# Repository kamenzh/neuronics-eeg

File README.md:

# Neuronic

An open development project for an affordable eight-channel EEG acquisition
PCB, ESP32 wireless streaming and PC-based signal processing and classification.

**Current revision: A0 — schematic and unrouted placement for bench review.**
There is no manufactured or body-validated Neuronic board yet. This repository
contains genuine KiCad source, not a manufacturing release.

**First time using KiCad? Read [START_HERE](docs/START_HERE.md).** Open
[`hardware/kicad/neuronic.kicad_pro`](hardware/kicad/neuronic.kicad_pro) in KiCad.

## System

```mermaid
flowchart TD
    E["8 contacts + reference"] --> P["Input networks"]
    P --> A["ADS1299: PGAs and simultaneous ADCs"]
    A -->|"3.3 V SPI"| M["External ESP32"]
    A --> B["Limited bias output: tenth contact"]
    M -->|"Wireless"| C["PC: recording and classification"]
    V["Battery and regulators"] --> A
```

| Parameter | A0 design target |
| --- | --- |
| Recording channels | 8 simultaneous |
| Contacts | 8 recording + 1 reference + 1 bias |
| Front end | ADS1299IPAG, programmable gain, 24-bit output |
| Initial rate | 250 samples/s/channel |
| Analog / ADC digital supplies | 5 V / 3.3 V |
| Input power | External 7-9 V battery pack; no charger |
| Controller interface | Generic 12-pin 3.3 V SPI header |
| PCB | 88 x 80 mm, four copper layers, placed and unrouted |

The ADS1299 already supplies the amplification and conversion. An additional
high-gain analog amplifier chain is not assumed. Nominal ADC bit depth is not
a claim of noise-free resolution, and more gain can reduce offset headroom.

## Repository map

| Path | Contents |
| --- | --- |
| `hardware/kicad/` | Main project, three schematic sheets, PCB, custom symbols and bundled footprints |
| `hardware/bom/` | Per-component review BOM; not an order list |
| `hardware/design.json` | Generated component/net/placement record |
| `hardware/validation/` | Exported netlist, connectivity audit, DRC, RC calculation and sheet previews |
| `hardware/fabrication/` | Release policy; no order-ready Gerbers |
| `firmware/` | Acquisition firmware specification; implementation pending |
| `software/` | PC receiver/recorder specification; implementation pending |
| `ml/` | Evaluation plan; no trained classifier yet |
| `experiments/` | Recording and validation protocols |
| `docs/` | Beginner guide, design decisions, open blockers and bench plan |
| `tools/` | Reproducible hardware generator and validation commands |
| `data/` | Local private recordings; contents ignored by Git |

The old CortexLink README is retained in `docs/archive/initial-README.md`.
The empty duplicate KiCad scaffolds were removed; their originals remain in
the repository history at `ae7d76e`.

## Verification

Read [the current status](hardware/validation/STATUS.md) before using the files.
Checks compare the **actual KiCad-exported netlist** with the source, component
footprints and an independent physical pin contract. They do not prove analog
performance, layout quality or body safety.

```bash
python tools/check_design.py
python tools/simulate_input.py
python tools/validate_kicad.py --kicad-cli /path/to/kicad-cli
```

The last command requires KiCad 8 or newer for CLI ERC/DRC. This unrouted
checkpoint is expected to fail release checks; errors are not excluded to
make the output look clean. GUI ERC/DRC instructions are in the beginner guide.

## Roadmap

- [x] Consolidate project and document circuit decisions.
- [x] Create editable KiCad sheets, footprint bundle, BOM and placed PCB.
- [x] Export and audit connectivity; perform limited ideal RC calculation.
- [ ] Close input-protection, connector, bias-loop and power-review blockers.
- [ ] Complete layout, plane design, routing, ERC and schematic-parity DRC.
- [ ] Select exact stocked parts and compare delivered assembly quotes.
- [ ] Fabricate a small prototype batch and complete bench tests.
- [ ] Implement and verify acquisition, raw recording and loss accounting.
- [ ] Review final body-connected design before scalp testing.
- [ ] Record repeatable EEG, then evaluate baselines and a CNN across sessions.

## Experiments and safety

The immediate target is trustworthy acquisition and a repeatable alpha
experiment. Intentional command classification follows measured signal quality.
EEG does not directly reveal arbitrary thoughts. Eye and muscle artifacts must
be checked, and train/test data must be separated by complete trials/sessions.

This is a body-connected engineering project, not a diagnostic device. A0 is
for bench development only. Do not attach it to a person. Final electrode
protection and fault paths need qualified review before any scalp recording.
Battery power, ERC and DRC alone do not establish safety. During approved
recording, use a self-contained battery arrangement and wireless communication,
with USB, chargers and mains-connected instruments disconnected.

## Sources and licensing

See [design decisions and primary sources](docs/DESIGN_DECISIONS.md),
[open blockers](docs/REVIEW_BLOCKERS.md) and [third-party notices](hardware/licenses/).
The repository's existing MIT license is preserved for original work. Bundled
KiCad library assets retain their own license and design-use exception. No
third-party EEG hardware project has been silently relicensed or included.

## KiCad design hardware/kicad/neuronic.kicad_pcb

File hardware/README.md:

# Hardware

Open `kicad/neuronic.kicad_pro`. Read `validation/STATUS.md` and
`../docs/START_HERE.md` first.

`design.json` is generated by `tools/generate_hardware.py` and describes the
component/net/placement checkpoint. It is not a substitute for the actual
KiCad schematic or DRC. `bom/bom-review.csv` lists candidate parts and unresolved
MPNs; it is not a purchase-ready BOM.

KiCad source, script and review docs belong in Git. Fabrication files should
only be exported for reviewed, tagged hardware revisions.

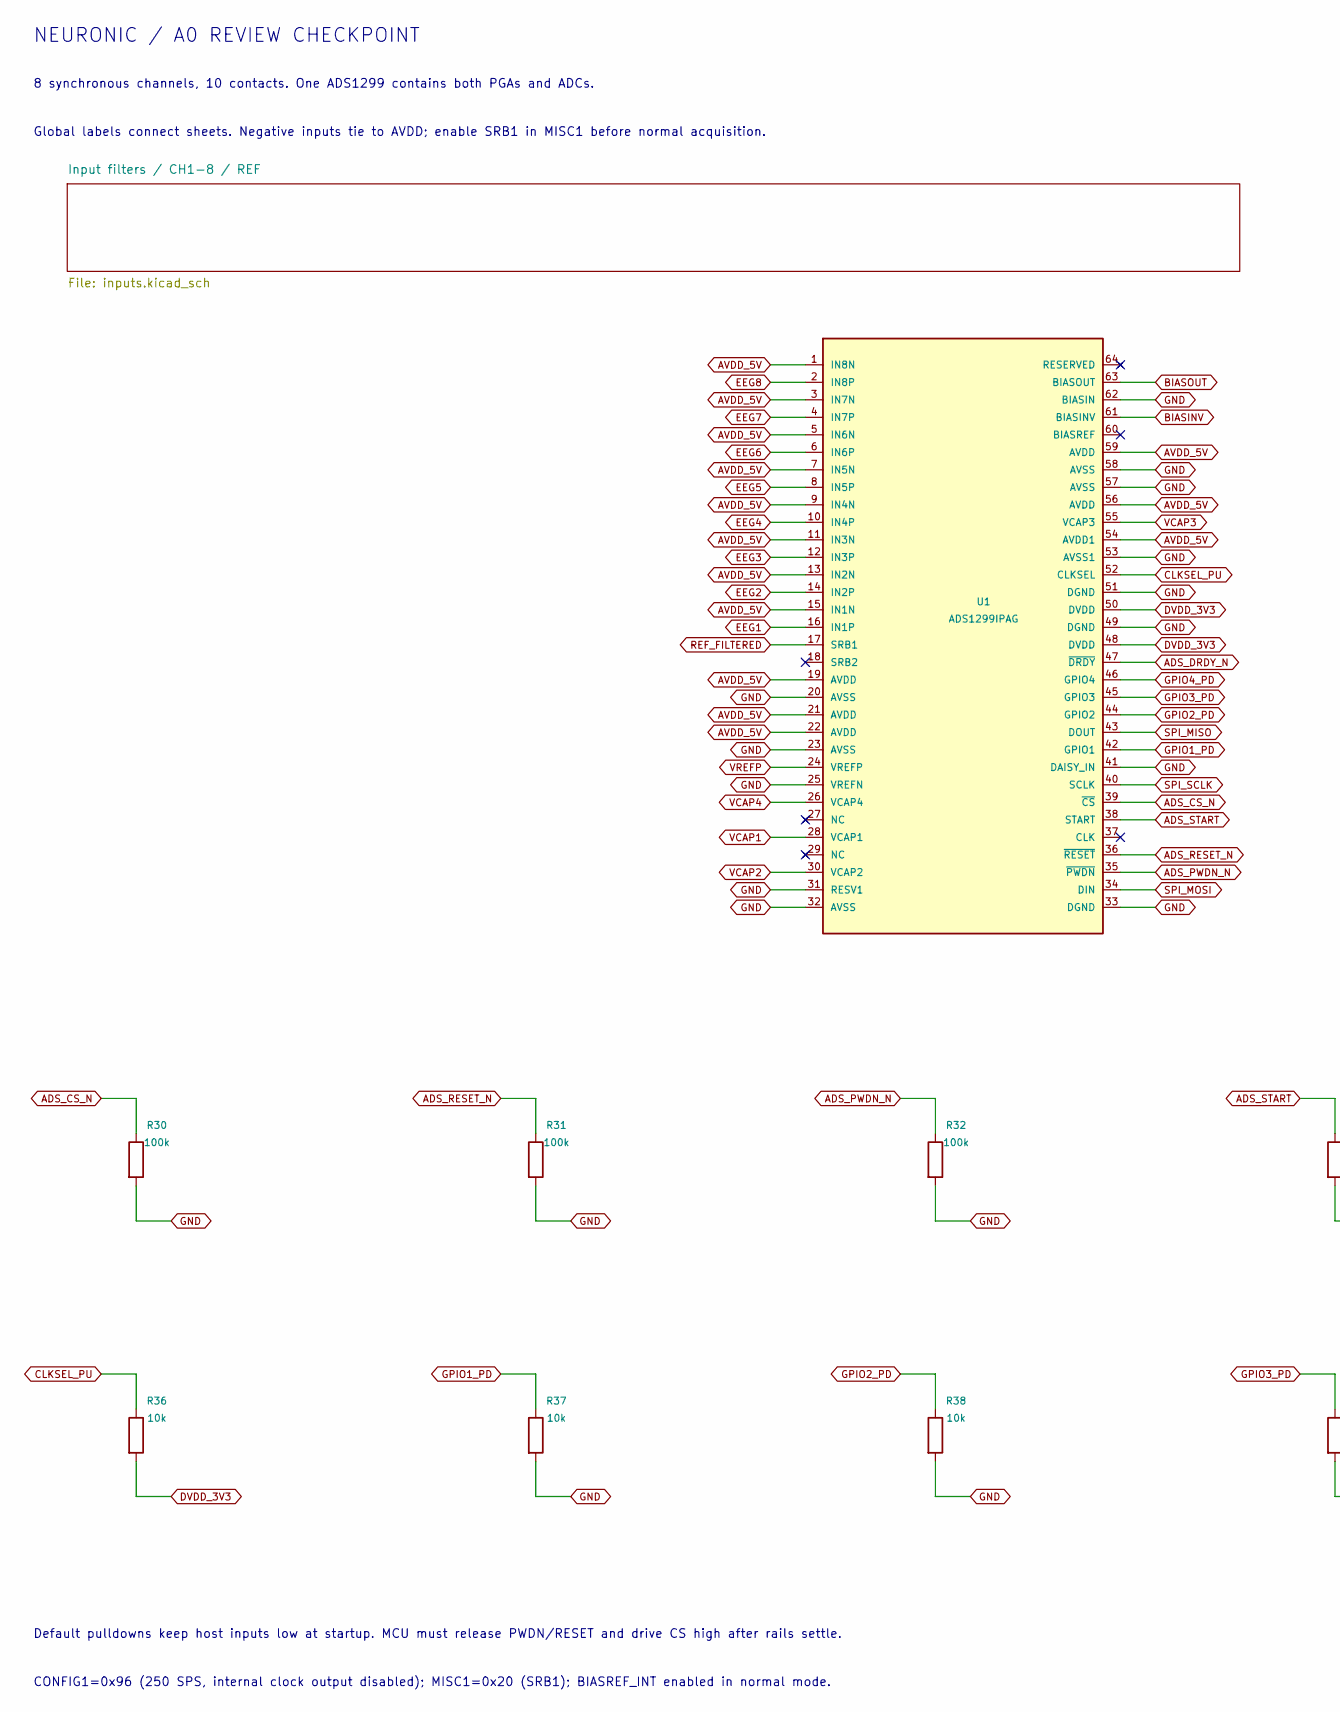
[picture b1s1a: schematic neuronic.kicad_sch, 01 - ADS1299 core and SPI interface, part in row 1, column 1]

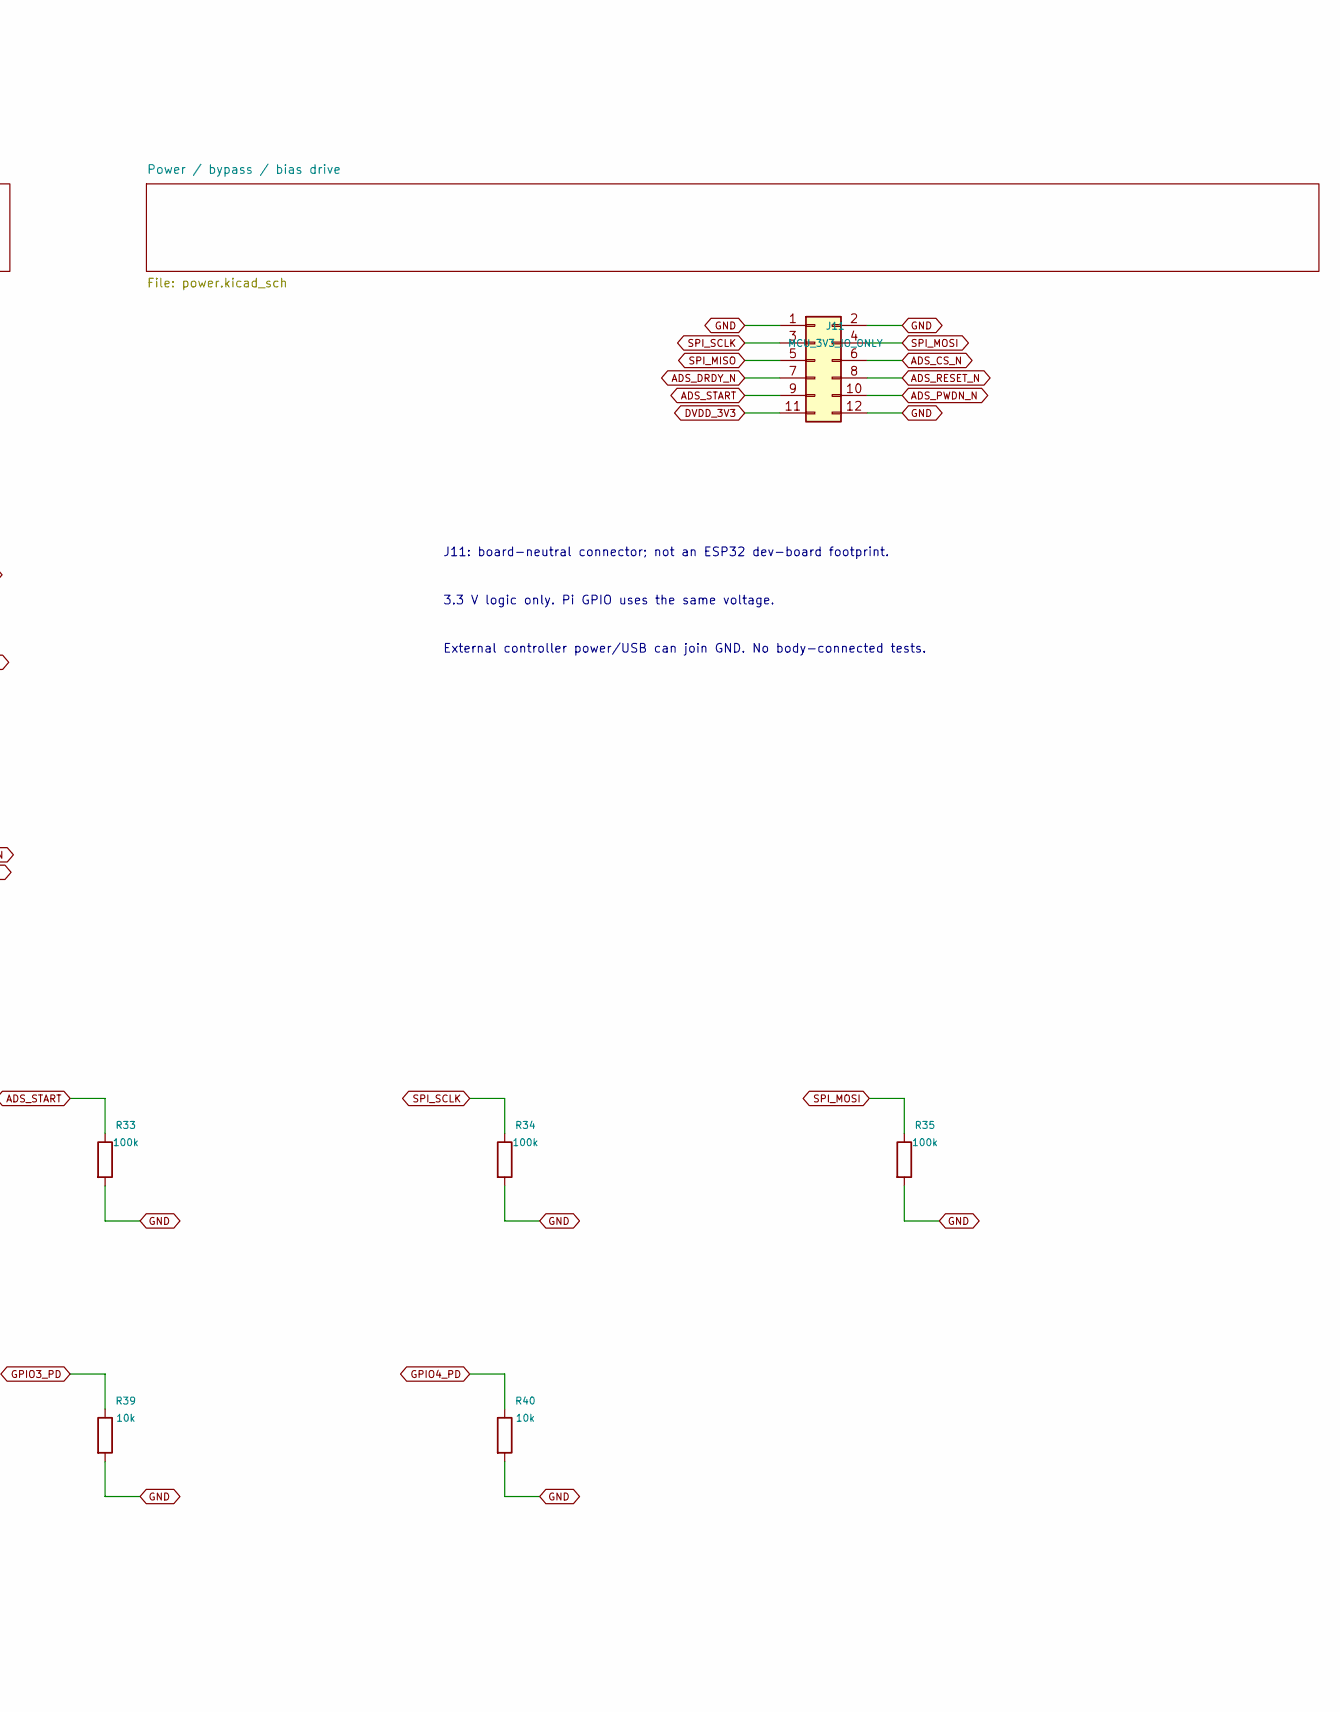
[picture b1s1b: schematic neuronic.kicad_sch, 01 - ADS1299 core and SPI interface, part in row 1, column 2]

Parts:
J11: MCU_3V3_IO_ONLY; PinHeader_2x06_P2.54mm_Vertical
R30, R31, R32, R33, R34, R35: 100k; R_0805_2012Metric
R36, R37, R38, R39, R40: 10k; R_0805_2012Metric
U1: ADS1299IPAG; TQFP-64_10x10mm_P0.5mm

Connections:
ADS_CS_N: J11.6, R30.1, U1.39 (~CS)
ADS_DRDY_N: J11.7, U1.47 (~DRDY)
ADS_PWDN_N: J11.10, R32.1, U1.35 (~PWDN)
ADS_RESET_N: J11.8, R31.1, U1.36 (~RESET)
ADS_START: J11.9, R33.1, U1.38 (START)
AVDD_5V: U1.1 (IN8N), U1.3 (IN7N), U1.5 (IN6N), U1.7 (IN5N), U1.9 (IN4N), U1.11 (IN3N), U1.13 (IN2N), U1.15 (IN1N), U1.19 (AVDD), U1.21 (AVDD), U1.22 (AVDD), U1.54 (AVDD1), U1.56 (AVDD), U1.59 (AVDD); also elsewhere on the board
BIASINV: U1.61 (BIASINV); also elsewhere on the board
BIASOUT: U1.63 (BIASOUT); also elsewhere on the board
CLKSEL_PU: R36.1, U1.52 (CLKSEL)
DVDD_3V3: J11.11, R36.2, U1.48 (DVDD), U1.50 (DVDD); also elsewhere on the board
EEG1: U1.16 (IN1P); also elsewhere on the board
EEG2: U1.14 (IN2P); also elsewhere on the board
EEG3: U1.12 (IN3P); also elsewhere on the board
EEG4: U1.10 (IN4P); also elsewhere on the board
EEG5: U1.8 (IN5P); also elsewhere on the board
EEG6: U1.6 (IN6P); also elsewhere on the board
EEG7: U1.4 (IN7P); also elsewhere on the board
EEG8: U1.2 (IN8P); also elsewhere on the board
GND: J11.1, J11.2, J11.12, R30.2, R31.2, R32.2, R33.2, R34.2, R35.2, R37.2, R38.2, R39.2, R40.2, U1.20 (AVSS), U1.23 (AVSS), U1.25 (VREFN), U1.31 (RESV1), U1.32 (AVSS), U1.33 (DGND), U1.41 (DAISY_IN), U1.49 (DGND), U1.51 (DGND), U1.53 (AVSS1), U1.57 (AVSS), U1.58 (AVSS), U1.62 (BIASIN); also elsewhere on the board
GPIO1_PD: R37.1, U1.42 (GPIO1)
GPIO2_PD: R38.1, U1.44 (GPIO2)
GPIO3_PD: R39.1, U1.45 (GPIO3)
GPIO4_PD: R40.1, U1.46 (GPIO4)
REF_FILTERED: U1.17 (SRB1); also elsewhere on the board
SPI_MISO: J11.5, U1.43 (DOUT)
SPI_MOSI: J11.4, R35.1, U1.34 (DIN)
SPI_SCLK: J11.3, R34.1, U1.40 (SCLK)
VCAP1: U1.28 (VCAP1); also elsewhere on the board
VCAP2: U1.30 (VCAP2); also elsewhere on the board
VCAP3: U1.55 (VCAP3); also elsewhere on the board
VCAP4: U1.26 (VCAP4); also elsewhere on the board
VREFP: U1.24 (VREFP); also elsewhere on the board

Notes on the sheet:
NEURONIC / A0 REVIEW CHECKPOINT
8 synchronous channels, 10 contacts. One ADS1299 contains both PGAs and ADCs.
Global labels connect sheets. Negative inputs tie to AVDD; enable SRB1 in MISC1 before normal acquisition.
J11: board-neutral connector; not an ESP32 dev-board footprint.
3.3 V logic only. Pi GPIO uses the same voltage.
External controller power/USB can join GND. No body-connected tests.
Default pulldowns keep host inputs low at startup. MCU must release PWDN/RESET and drive CS high after rails settle.
CONFIG1=0x96 (250 SPS, internal clock output disabled); MISC1=0x20 (SRB1); BIASREF_INT enabled in normal mode.

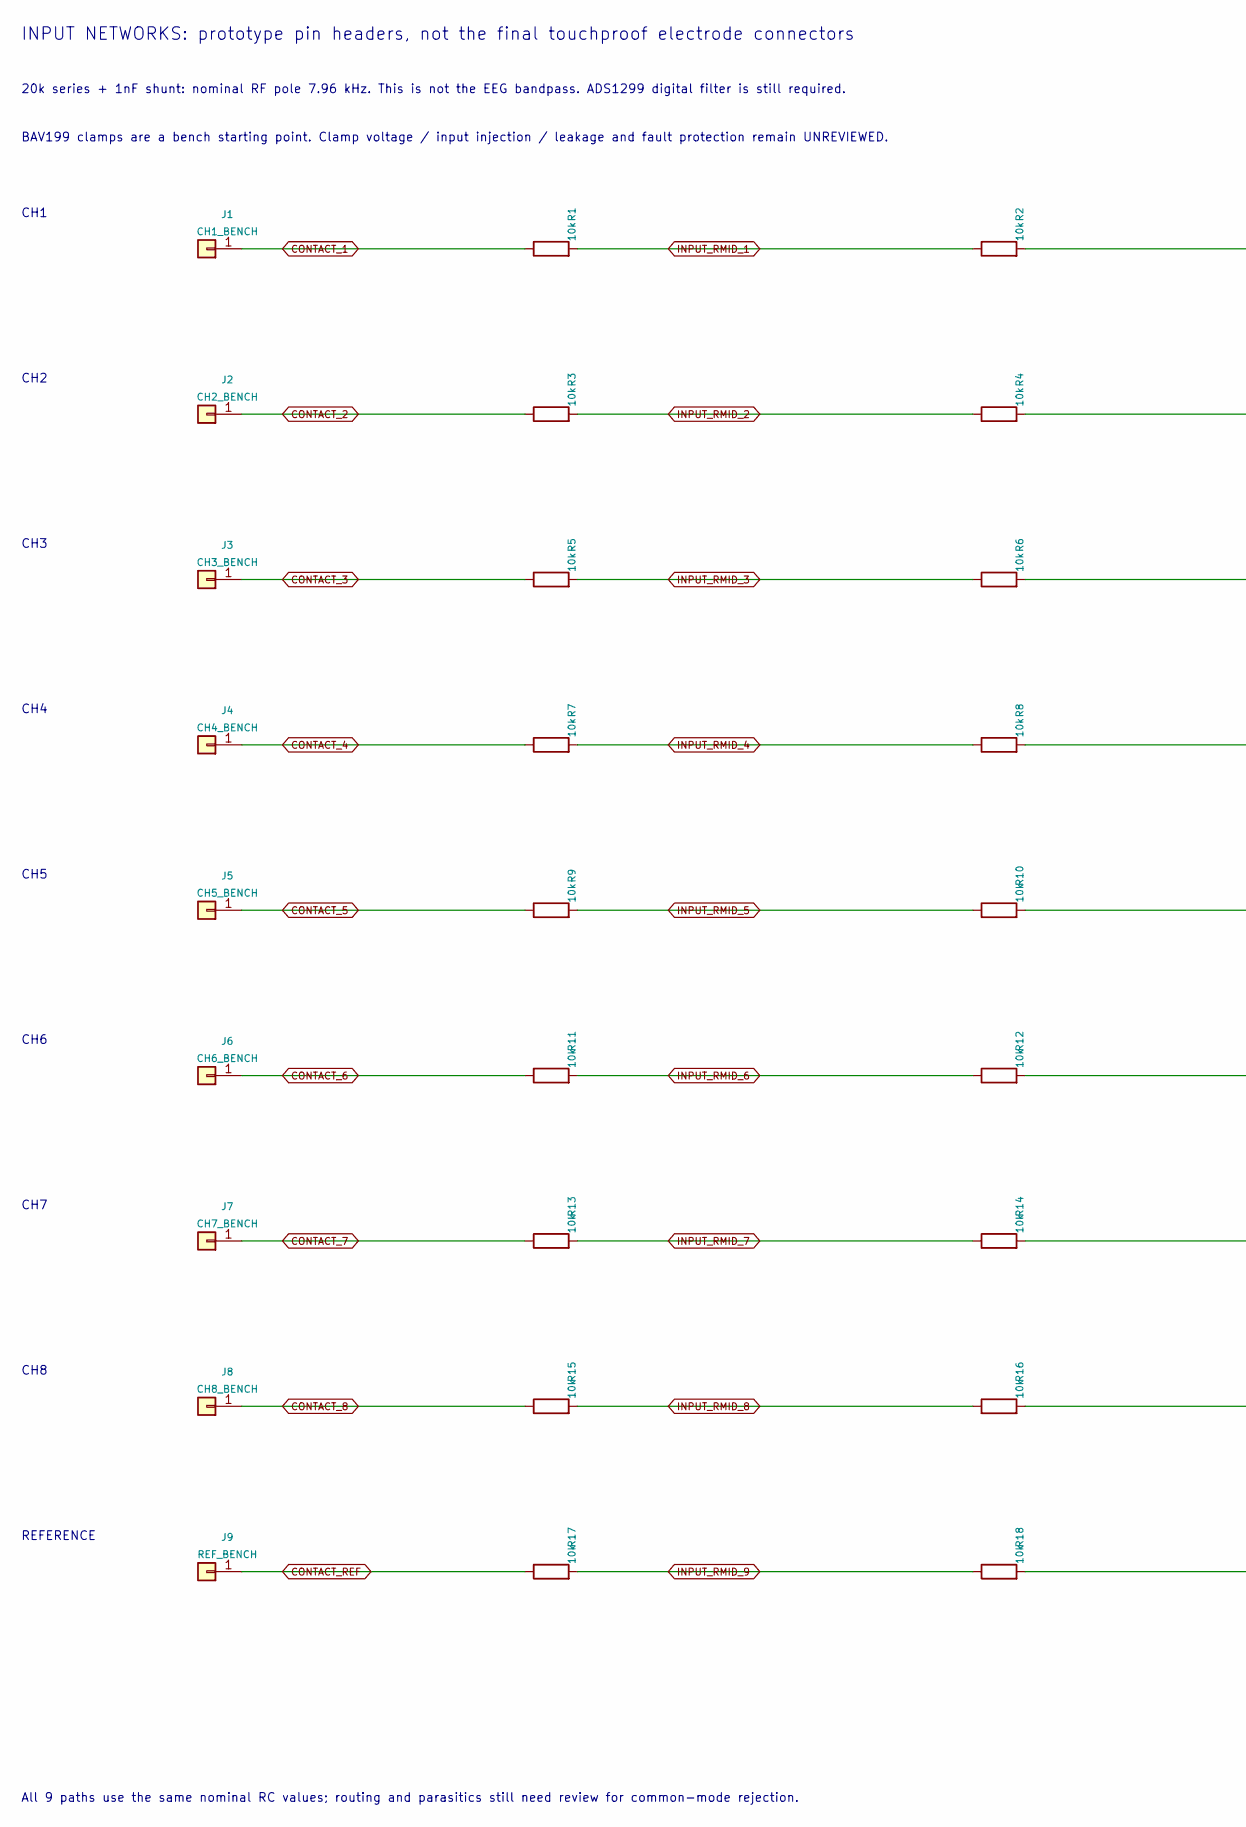
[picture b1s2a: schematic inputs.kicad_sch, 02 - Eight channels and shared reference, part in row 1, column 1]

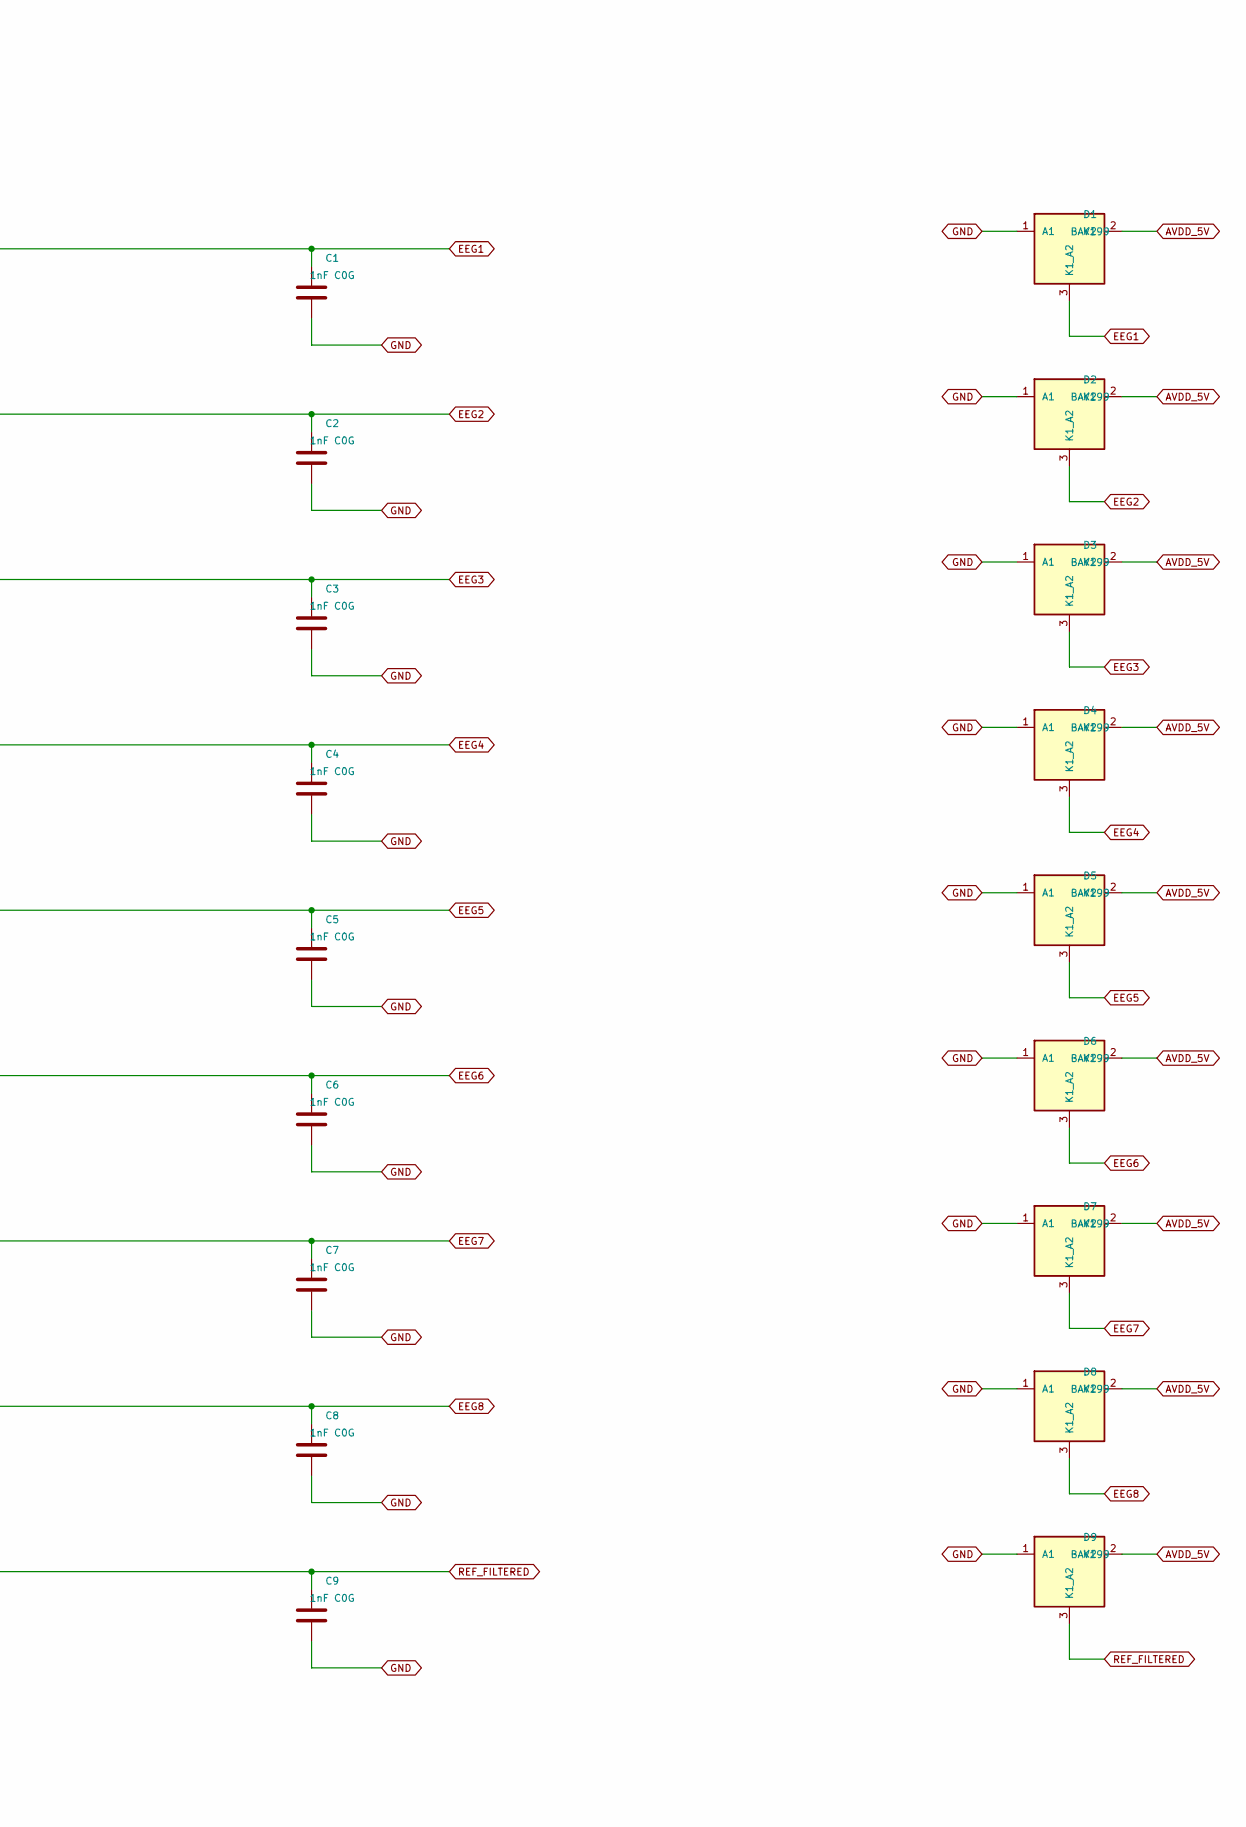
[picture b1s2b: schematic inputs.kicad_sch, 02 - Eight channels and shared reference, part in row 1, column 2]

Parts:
C1, C2, C3, C4, C5, C6, C7, C8, C9: 1nF C0G; C_0805_2012Metric
D1, D2, D3, D4, D5, D6, D7, D8, D9: BAV199; SOT-23
J1: CH1_BENCH; PinHeader_1x01_P2.54mm_Vertical
J2: CH2_BENCH; PinHeader_1x01_P2.54mm_Vertical
J3: CH3_BENCH; PinHeader_1x01_P2.54mm_Vertical
J4: CH4_BENCH; PinHeader_1x01_P2.54mm_Vertical
J5: CH5_BENCH; PinHeader_1x01_P2.54mm_Vertical
J6: CH6_BENCH; PinHeader_1x01_P2.54mm_Vertical
J7: CH7_BENCH; PinHeader_1x01_P2.54mm_Vertical
J8: CH8_BENCH; PinHeader_1x01_P2.54mm_Vertical
J9: REF_BENCH; PinHeader_1x01_P2.54mm_Vertical
R1, R2, R3, R4, R5, R6, R7, R8, R9, R10, R11, R12, R13, R14, R15, R16, R17, R18: 10k; R_0805_2012Metric

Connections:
AVDD_5V: D1.2 (K2), D2.2 (K2), D3.2 (K2), D4.2 (K2), D5.2 (K2), D6.2 (K2), D7.2 (K2), D8.2 (K2), D9.2 (K2); also elsewhere on the board
CONTACT_1: J1.1, R1.1
CONTACT_2: J2.1, R3.1
CONTACT_3: J3.1, R5.1
CONTACT_4: J4.1, R7.1
CONTACT_5: J5.1, R9.1
CONTACT_6: J6.1, R11.1
CONTACT_7: J7.1, R13.1
CONTACT_8: J8.1, R15.1
CONTACT_REF: J9.1, R17.1
EEG1: C1.1, D1.3 (K1_A2), R2.2; also elsewhere on the board
EEG2: C2.1, D2.3 (K1_A2), R4.2; also elsewhere on the board
EEG3: C3.1, D3.3 (K1_A2), R6.2; also elsewhere on the board
EEG4: C4.1, D4.3 (K1_A2), R8.2; also elsewhere on the board
EEG5: C5.1, D5.3 (K1_A2), R10.2; also elsewhere on the board
EEG6: C6.1, D6.3 (K1_A2), R12.2; also elsewhere on the board
EEG7: C7.1, D7.3 (K1_A2), R14.2; also elsewhere on the board
EEG8: C8.1, D8.3 (K1_A2), R16.2; also elsewhere on the board
GND: C1.2, C2.2, C3.2, C4.2, C5.2, C6.2, C7.2, C8.2, C9.2, D1.1 (A1), D2.1 (A1), D3.1 (A1), D4.1 (A1), D5.1 (A1), D6.1 (A1), D7.1 (A1), D8.1 (A1), D9.1 (A1); also elsewhere on the board
INPUT_RMID_1: R1.2, R2.1
INPUT_RMID_2: R3.2, R4.1
INPUT_RMID_3: R5.2, R6.1
INPUT_RMID_4: R7.2, R8.1
INPUT_RMID_5: R9.2, R10.1
INPUT_RMID_6: R11.2, R12.1
INPUT_RMID_7: R13.2, R14.1
INPUT_RMID_8: R15.2, R16.1
INPUT_RMID_9: R17.2, R18.1
REF_FILTERED: C9.1, D9.3 (K1_A2), R18.2; also elsewhere on the board

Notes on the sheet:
INPUT NETWORKS: prototype pin headers, not the final touchproof electrode connectors
20k series + 1nF shunt: nominal RF pole 7.96 kHz. This is not the EEG bandpass. ADS1299 digital filter is still required.
BAV199 clamps are a bench starting point. Clamp voltage / input injection / leakage and fault protection remain UNREVIEWED.
CH1
CH2
CH3
CH4
CH5
CH6
CH7
CH8
REFERENCE
All 9 paths use the same nominal RC values; routing and parasitics still need review for common-mode rejection.

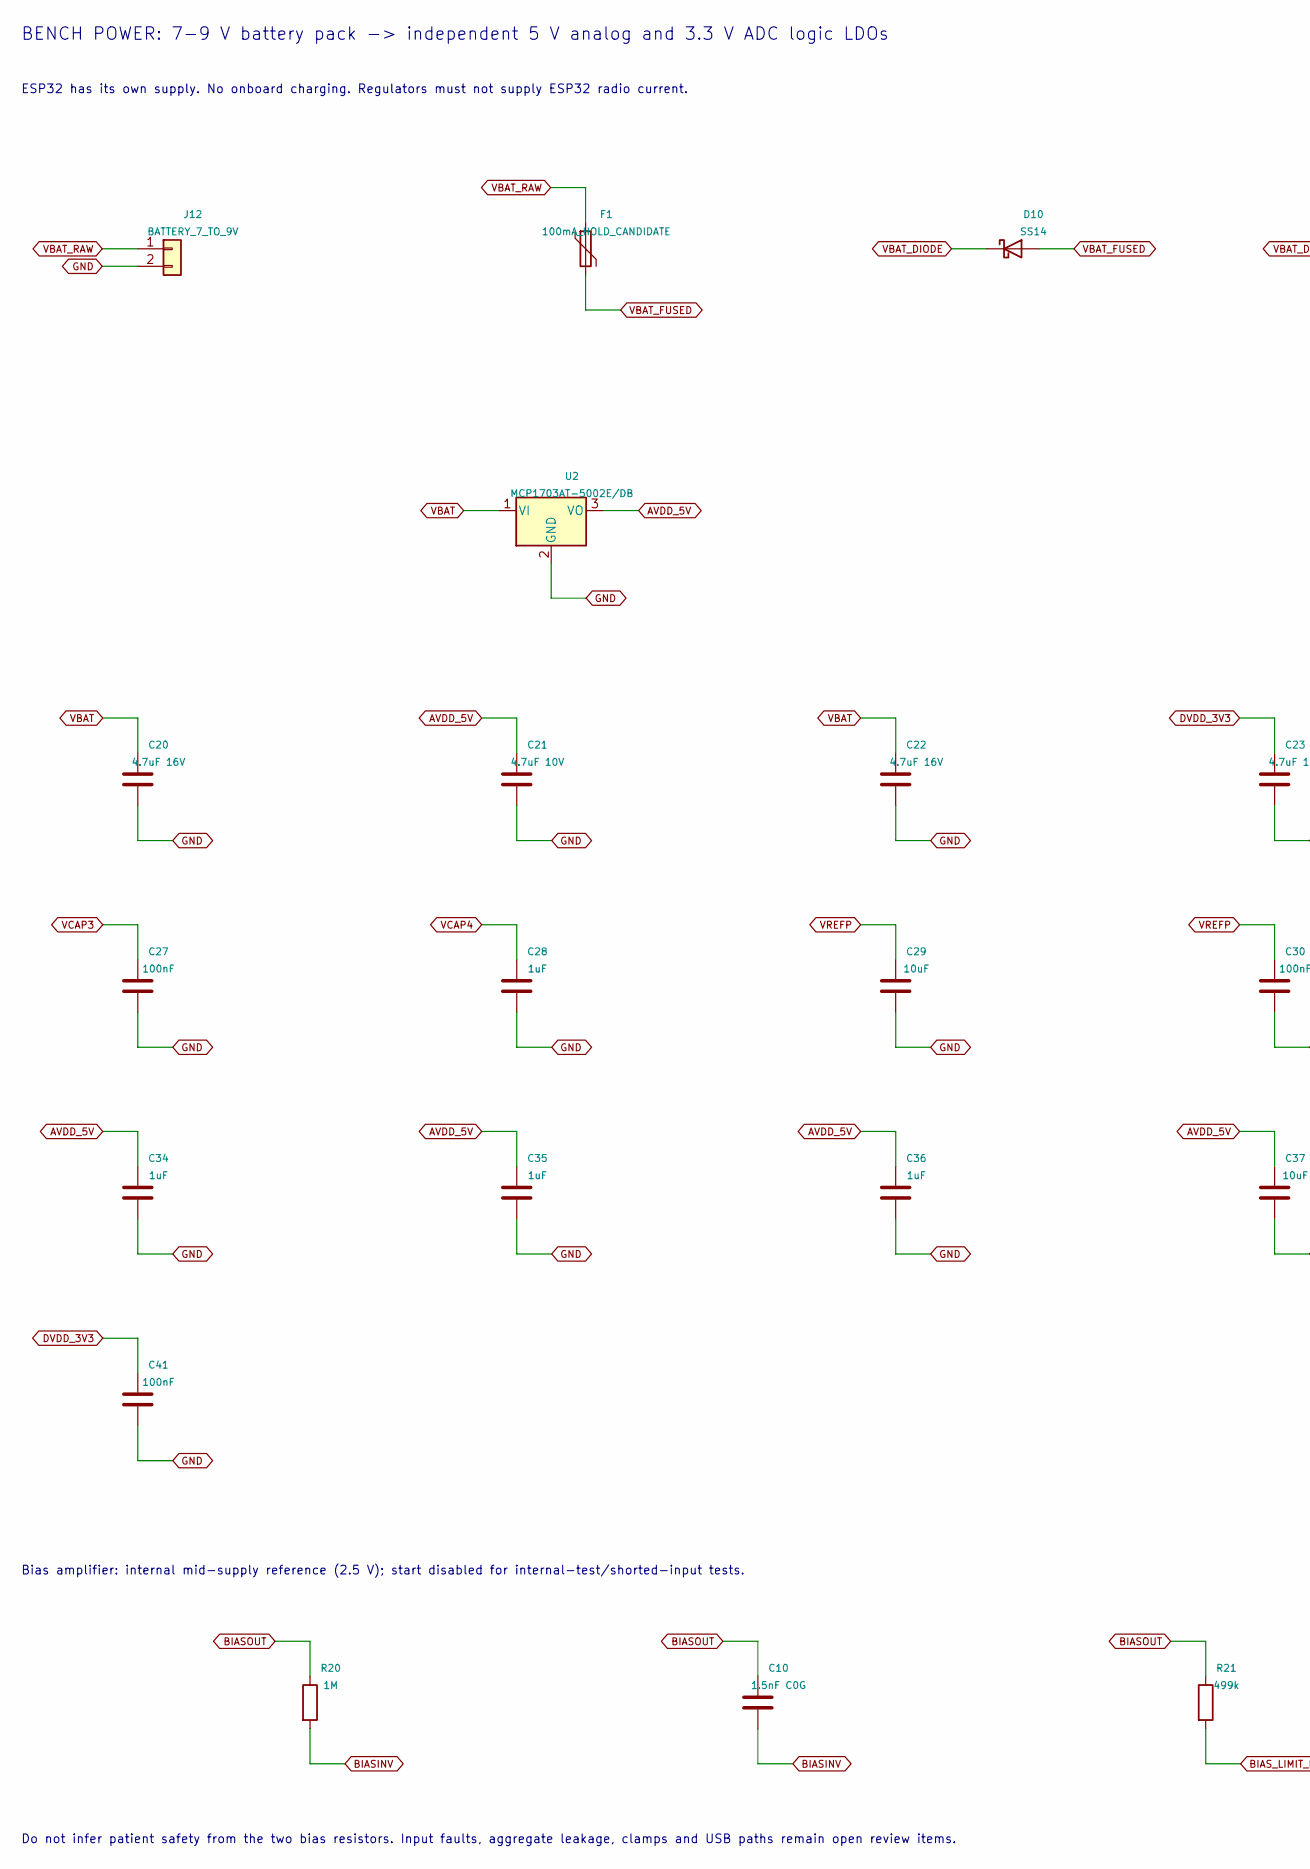
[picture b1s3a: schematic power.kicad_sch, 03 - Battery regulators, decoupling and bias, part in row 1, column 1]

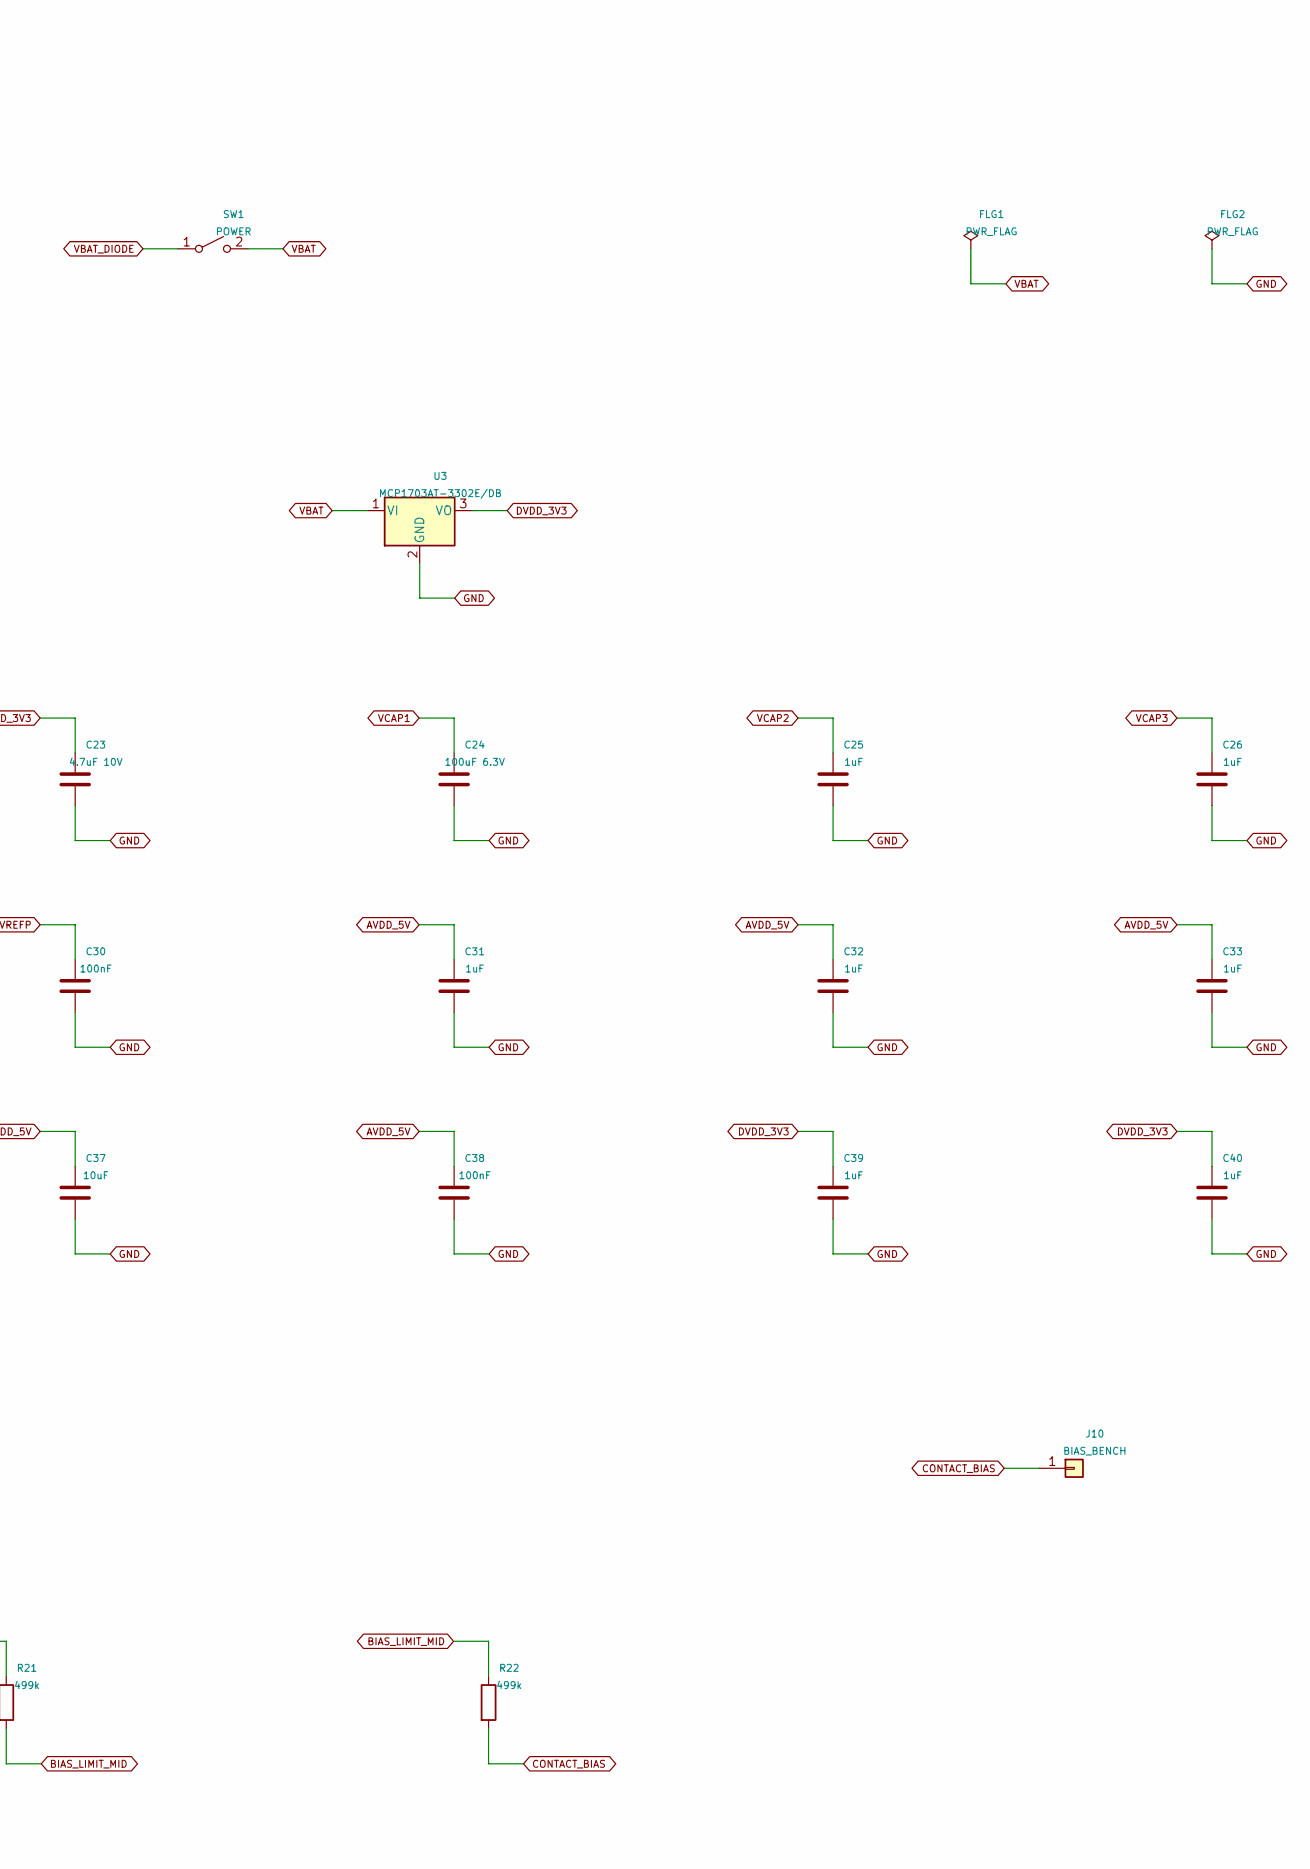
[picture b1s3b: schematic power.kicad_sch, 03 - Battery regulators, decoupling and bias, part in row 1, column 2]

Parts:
C10: 1.5nF C0G; C_0805_2012Metric
C20, C22: 4.7uF 16V; C_0805_2012Metric
C21, C23: 4.7uF 10V; C_0805_2012Metric
C24: 100uF 6.3V; C_1210_3225Metric
C25, C26, C28, C31, C32, C33, C34, C35, C36, C39, C40: 1uF; C_0805_2012Metric
C27, C30, C38, C41: 100nF; C_0805_2012Metric
C29, C37: 10uF; C_0805_2012Metric
D10: SS14; D_SMA
F1: 100mA_HOLD_CANDIDATE; R_0805_2012Metric
FLG1, FLG2: PWR_FLAG
J10: BIAS_BENCH; PinHeader_1x01_P2.54mm_Vertical
J12: BATTERY_7_TO_9V; PinHeader_1x02_P2.54mm_Vertical
R20: 1M; R_0805_2012Metric
R21, R22: 499k; R_0805_2012Metric
SW1: POWER; PinHeader_1x02_P2.54mm_Vertical
U2: MCP1703AT-5002E/DB; SOT-223-3_TabPin2
U3: MCP1703AT-3302E/DB; SOT-223-3_TabPin2

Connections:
AVDD_5V: C21.1, C31.1, C32.1, C33.1, C34.1, C35.1, C36.1, C37.1, C38.1, U2.3 (VO); also elsewhere on the board
BIASINV: C10.2, R20.2; also elsewhere on the board
BIASOUT: C10.1, R20.1, R21.1; also elsewhere on the board
BIAS_LIMIT_MID: R21.2, R22.1
CONTACT_BIAS: J10.1, R22.2
DVDD_3V3: C23.1, C39.1, C40.1, C41.1, U3.3 (VO); also elsewhere on the board
GND: C20.2, C21.2, C22.2, C23.2, C24.2, C25.2, C26.2, C27.2, C28.2, C29.2, C30.2, C31.2, C32.2, C33.2, C34.2, C35.2, C36.2, C37.2, C38.2, C39.2, C40.2, C41.2, FLG2.1, J12.2, U2.2 (GND), U3.2 (GND); also elsewhere on the board
VBAT: C20.1, C22.1, FLG1.1, SW1.2 (B), U2.1 (VI), U3.1 (VI)
VBAT_DIODE: D10.1 (K), SW1.1 (A)
VBAT_FUSED: D10.2 (A), F1.2
VBAT_RAW: F1.1, J12.1
VCAP1: C24.1; also elsewhere on the board
VCAP2: C25.1; also elsewhere on the board
VCAP3: C26.1, C27.1; also elsewhere on the board
VCAP4: C28.1; also elsewhere on the board
VREFP: C29.1, C30.1; also elsewhere on the board

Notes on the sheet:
BENCH POWER: 7-9 V battery pack -> independent 5 V analog and 3.3 V ADC logic LDOs
ESP32 has its own supply. No onboard charging. Regulators must not supply ESP32 radio current.
Bias amplifier: internal mid-supply reference (2.5 V); start disabled for internal-test/shorted-input tests.
Do not infer patient safety from the two bias resistors. Input faults, aggregate leakage, clamps and USB paths remain open review items.

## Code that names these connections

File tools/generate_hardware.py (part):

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    '23':'AVSS', '24':'VREFP', '25':'VREFN', '26':'VCAP4', '27':'NC', '28':'VCAP1',
    '29':'NC', '30':'VCAP2', '31':'RESV1', '32':'AVSS', '33':'DGND', '34':'DIN',
    '35':'~{PWDN}', '36':'~{RESET}', '37':'CLK', '38':'START', '39':'~{CS}', '40':'SCLK',
    '41':'DAISY_IN', '42':'GPIO1', '43':'DOUT', '44':'GPIO2', '45':'GPIO3', '46':'GPIO4',
    '47':'~{DRDY}', '48':'DVDD', '49':'DGND', '50':'DVDD', '51':'DGND', '52':'CLKSEL',
    '53':'AVSS1', '54':'AVDD1', '55':'VCAP3', '56':'AVDD', '57':'AVSS', '58':'AVSS',
    '59':'AVDD', '60':'BIASREF', '61':'BIASINV', '62':'BIASIN', '63':'BIASOUT', '64':'RESERVED'}
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        typ = 'input'
        if name.startswith(('AVDD','AVSS','DVDD','DGND')): typ='power_in'
        elif name in ['DOUT','~{DRDY}','BIASOUT'] or name.startswith('VCAP'): typ='output'
        elif name.startswith('GPIO') or name in ['SRB1','SRB2','VREFP','BIASINV']: typ='bidirectional'
        elif name in ['NC','RESERVED']: typ='no_connect'
        pins.append((str(i), name, typ, -22.86 if side else 22.86, y, 0 if side else 180))
    LIB['Neuronic:ADS1299IPAG'] = custom_symbol('ADS1299IPAG', pins, 20.32, 43.18,
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    nets.update({'17':'REF_FILTERED','18':None,'19':'AVDD_5V','20':'GND','21':'AVDD_5V','22':'AVDD_5V','23':'GND',
        '24':'VREFP','25':'GND','26':'VCAP4','27':None,'28':'VCAP1','29':None,'30':'VCAP2','31':'GND','32':'GND',
        '33':'GND','34':'SPI_MOSI','35':'ADS_PWDN_N','36':'ADS_RESET_N','37':None,'38':'ADS_START','39':'ADS_CS_N',
        '40':'SPI_SCLK','41':'GND','42':'GPIO1_PD','43':'SPI_MISO','44':'GPIO2_PD','45':'GPIO3_PD','46':'GPIO4_PD',
        '47':'ADS_DRDY_N','48':'DVDD_3V3','49':'GND','50':'DVDD_3V3','51':'GND','52':'CLKSEL_PU',
        '53':'GND','54':'AVDD_5V','55':'VCAP3','56':'AVDD_5V','57':'GND','58':'GND','59':'AVDD_5V',
        '60':None,'61':'BIASINV','62':'GND','63':'BIASOUT','64':None})
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    root.text('3.3 V logic only. Pi GPIO uses the same voltage.',258,100)
    root.text('External controller power/USB can join GND. No body-connected tests.',258,107)
    rnum=30
    for i,(net,rail) in enumerate([('ADS_CS_N','GND'),('ADS_RESET_N','GND'),('ADS_PWDN_N','GND'),('ADS_START','GND'),('SPI_SCLK','GND'),('SPI_MOSI','GND'),('CLKSEL_PU','DVDD_3V3'),('GPIO1_PD','GND'),('GPIO2_PD','GND'),('GPIO3_PD','GND'),('GPIO4_PD','GND')]):
        x=35+(i%6)*58;y=181+(i//6)*40
        add_rc(root,f'R{rnum+i}','100k' if i<6 else '10k',net,rail,x,y,(116+(i%4)*5,103+(i//4)*7))
    root.text('Default pulldowns keep host inputs low at startup. MCU must release PWDN/RESET and drive CS high after rails settle.',20,250)
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
    power.text('BENCH POWER: 7-9 V battery pack -> independent 5 V analog and 3.3 V ADC logic LDOs',18,17,1.8)
    power.text('ESP32 has its own supply. No onboard charging. Regulators must not supply ESP32 radio current.',18,25)
    power.part('J12','Connector_Generic:Conn_01x02','BATTERY_7_TO_9V',40,48,{'1':'VBAT_RAW','2':'GND'},'Neuronic:PinHeader_1x02_P2.54mm_Vertical',xy=(130,61))
    power.part('F1','Device:Polyfuse','100mA_HOLD_CANDIDATE',100,48,{'1':'VBAT_RAW','2':'VBAT_FUSED'},RFP,xy=(124,60),note='Choose exact voltage/current/thermal rating before release')
    power.part('D10','Device:D_Schottky','SS14',162,48,{'2':'VBAT_FUSED','1':'VBAT_DIODE'},'Neuronic:D_SMA',xy=(117,60),note='Reverse polarity protection; verify thermal behavior',mpn='SS14')
    power.part('SW1','Switch:SW_SPST','POWER',220,48,{'1':'VBAT_DIODE','2':'VBAT'},'Neuronic:PinHeader_1x02_P2.54mm_Vertical',xy=(109,60),note='Header for an offboard SPST switch')
    for i,(value,rail) in enumerate([('MCP1703AT-5002E/DB','AVDD_5V'),('MCP1703AT-3302E/DB','DVDD_3V3')]):
        power.part(f'U{i+2}','Regulator_Linear:MCP1703Ax-330xxDB',value,95+155*i,86,{'1':'VBAT','2':'GND','3':rail},'Neuronic:SOT-223-3_TabPin2',xy=(109+i*14,72),note='Fixed output variant; matching footprint pin1 VIN pin2 GND pin3 VOUT',mpn=value)
    power.part('FLG1','power:PWR_FLAG','PWR_FLAG',330,48,{'1':'VBAT'})
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    add_rc(power,'C10','1.5nF C0G','BIASOUT','BIASINV',125,259,(95,72),kind='C')
    add_rc(power,'R21','499k','BIASOUT','BIAS_LIMIT_MID',190,259,(86,114),rot=90)
    add_rc(power,'R22','499k','BIAS_LIMIT_MID','CONTACT_BIAS',260,259,(75,128),rot=90)
    power.part('J10','Connector_Generic:Conn_01x01','BIAS_BENCH',345,225,{'1':'CONTACT_BIAS'},'Neuronic:PinHeader_1x01_P2.54mm_Vertical',xy=(57,128),note='Bias output. Not protective earth. Bench connector only.')
    power.text('Do not infer patient safety from the two bias resistors. Input faults, aggregate leakage, clamps and USB paths remain open review items.',18,279)
    for s in SHEETS.values():s.save(s is root)
    return PARTS
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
